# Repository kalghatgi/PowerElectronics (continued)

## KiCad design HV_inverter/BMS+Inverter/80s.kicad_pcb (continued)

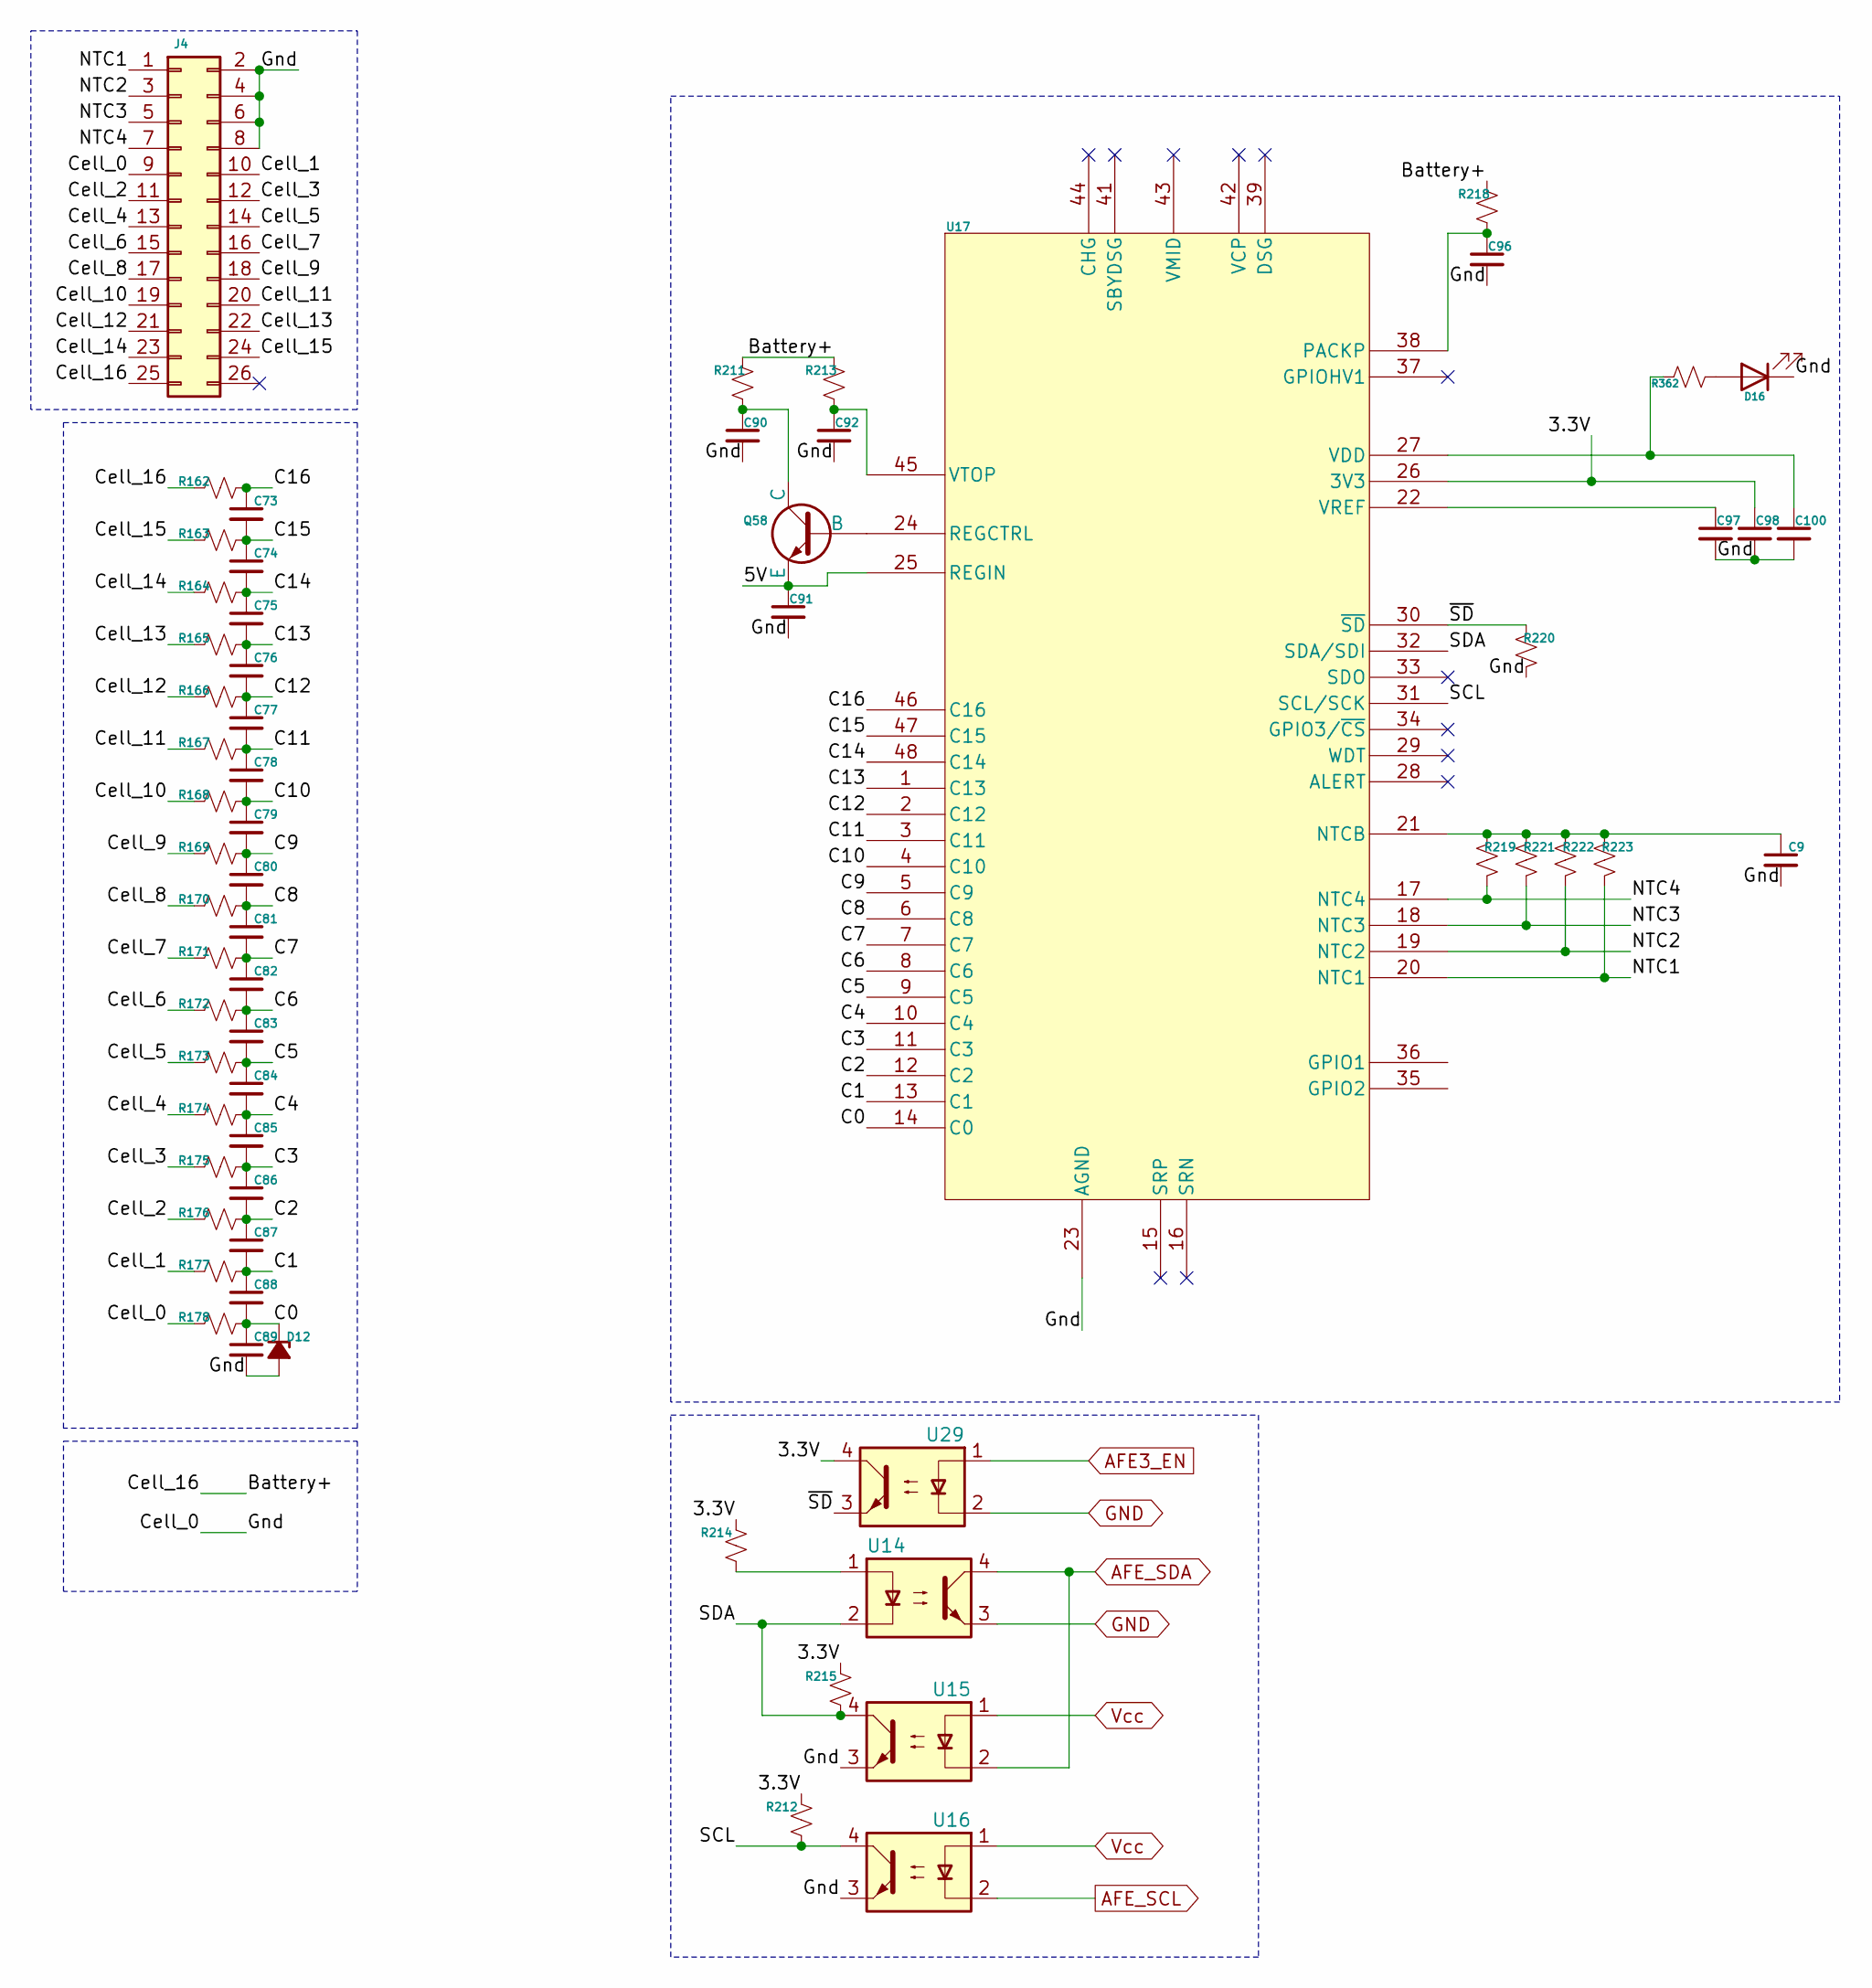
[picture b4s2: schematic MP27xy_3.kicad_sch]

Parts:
C9, C73, C74, C75, C76, C77, C78, C79, C80, C81, C82, C83, C84, C85, C86, C87, C88, C89: 10000pF, >=10V, 0402; C_0402_1005Metric; MPN grm155r61c103ka01d
C90: 1uF, >=100V, 0805; C_0805_2012Metric; MPN grm21bc72a105ke01l
C91: 3.3uF, >=10V, 0402; C_0402_1005Metric
C92: 0.47uF, >=100V, 0805; C_0805_2012Metric; MPN cc0805kkx7r0bb474
C96: 10nF, >=100V, 0805; C_0805_2012Metric; MPN c0805c103k1ractu
C97, C98, C100: 1uF, >=6.3V, 0402; C_0402_1005Metric; MPN cl05a105kq5nnnc
D12: VR=3.3V; D_SOD-323; MPN bzx384c3v3-e3-08
D16: LED-Red 0402; LED_0402_1005Metric
J4: 2x13 pin; IDC-Header_2x13_P2.54mm_Horizontal
Q58: NPN, 80V, 0.5A; SOT-23; MPN mmbt5550lt1g
R162, R163, R164, R165, R166, R167, R168, R169, R170, R171, R172, R173, R174, R175, R176, R177, R178: 1K, >=62.5mW, 0402; R_0402_1005Metric; MPN mcwr04x1001ftl
R211: 500E, >=100mW, 0603; R_0603_1608Metric; MPN rt0603brc07500rl
R212, R214, R215: 1.5K, >=62.5mW, 0402; R_0402_1005Metric; MPN mcwr04x1501ftl
R213: 20E, >=100mW, 0603; R_0603_1608Metric; MPN mcwr06x20r0ftl
R218: 100E, >=100mW, 0603; R_0603_1608Metric; MPN mcwr06x101-jtl
R219, R220, R221, R222, R223, R362: 10K, >=62.5mW, 0402; R_0402_1005Metric; MPN mcwr04x1002ftl
U14, U15, U16, U29: PC817; DIP-4_W7.62mm
U17: MP2787; TQFP-48_7x7mm_P0.5mm; MPN MP2787DFP-0001-T

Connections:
/CMU3/3.3V: C98.1, R212.2, R214.2, R215.2, U17.26 (3V3), U29.4
/CMU3/5V: C91.1, Q58.2 (E), U17.25 (REGIN)
/CMU3/Battery+: J4.25, R162.2, R211.2, R213.2, R218.2
/CMU3/C0: C88.2, C89.1, D12.1 (K), R178.1, U17.14 (C0)
/CMU3/C1: C87.2, C88.1, R177.1, U17.13 (C1)
/CMU3/C2: C86.2, C87.1, R176.1, U17.12 (C2)
/CMU3/C3: C85.2, C86.1, R175.1, U17.11 (C3)
/CMU3/C4: C84.2, C85.1, R174.1, U17.10 (C4)
/CMU3/C5: C83.2, C84.1, R173.1, U17.9 (C5)
/CMU3/C6: C82.2, C83.1, R172.1, U17.8 (C6)
/CMU3/C7: C81.2, C82.1, R171.1, U17.7 (C7)
/CMU3/C8: C80.2, C81.1, R170.1, U17.6 (C8)
/CMU3/C9: C79.2, C80.1, R169.1, U17.5 (C9)
/CMU3/C10: C78.2, C79.1, R168.1, U17.4 (C10)
/CMU3/C11: C77.2, C78.1, R167.1, U17.3 (C11)
/CMU3/C12: C76.2, C77.1, R166.1, U17.2 (C12)
/CMU3/C13: C75.2, C76.1, R165.1, U17.1 (C13)
/CMU3/C14: C74.2, C75.1, R164.1, U17.48 (C14)
/CMU3/C15: C73.2, C74.1, R163.1, U17.47 (C15)
/CMU3/C16: C73.1, R162.1, U17.46 (C16)
/CMU3/Cell_0: C9.2, C89.2, C90.2, C91.2, C92.2, C96.2, C97.2, C98.2, C100.2, D12.2 (A), D16.1 (K), J4.2, J4.4, J4.6, J4.8, J4.9, R178.2, R220.2, U15.3, U16.3, U17.23 (AGND)
/CMU3/Cell_1: J4.10, R177.2
/CMU3/Cell_2: J4.11, R176.2
/CMU3/Cell_3: J4.12, R175.2
/CMU3/Cell_4: J4.13, R174.2
/CMU3/Cell_5: J4.14, R173.2
/CMU3/Cell_6: J4.15, R172.2
/CMU3/Cell_7: J4.16, R171.2
/CMU3/Cell_8: J4.17, R170.2
/CMU3/Cell_9: J4.18, R169.2
/CMU3/Cell_10: J4.19, R168.2
/CMU3/Cell_11: J4.20, R167.2
/CMU3/Cell_12: J4.21, R166.2
/CMU3/Cell_13: J4.22, R165.2
/CMU3/Cell_14: J4.23, R164.2
/CMU3/Cell_15: J4.24, R163.2
/CMU3/NTC1: J4.1, R223.2, U17.20 (NTC1)
/CMU3/NTC2: J4.3, R222.2, U17.19 (NTC2)
/CMU3/NTC3: J4.5, R221.2, U17.18 (NTC3)
/CMU3/NTC4: J4.7, R219.2, U17.17 (NTC4)
/CMU3/SCL: R212.1, U16.4, U17.31 (SCL/SCK)
/CMU3/SDA: R215.1, U14.2, U15.4, U17.32 (SDA/SDI)
/CMU3/~SD: R220.1, U17.30 (~SD), U29.3
AFE3_EN: U29.1; also elsewhere on the board
AFE_SCL: U16.2; also elsewhere on the board
AFE_SDA: U14.4, U15.2; also elsewhere on the board
GND: U14.3, U29.2; also elsewhere on the board
unnamed: D16.2 (A), R362.1
unnamed: Q58.1 (B), U17.24 (REGCTRL)
unnamed: C90.1, Q58.3 (C), R211.1
unnamed: R214.1, U14.1
unnamed: C9.1, R219.1, R221.1, R222.1, R223.1, U17.21 (NTCB)
unnamed: C96.1, R218.1, U17.38 (PACKP)
unnamed: C100.1, R362.2, U17.27 (VDD)
unnamed: C97.1, U17.22 (VREF)
unnamed: C92.1, R213.1, U17.45 (VTOP)
Vcc: U15.1, U16.1; also elsewhere on the board

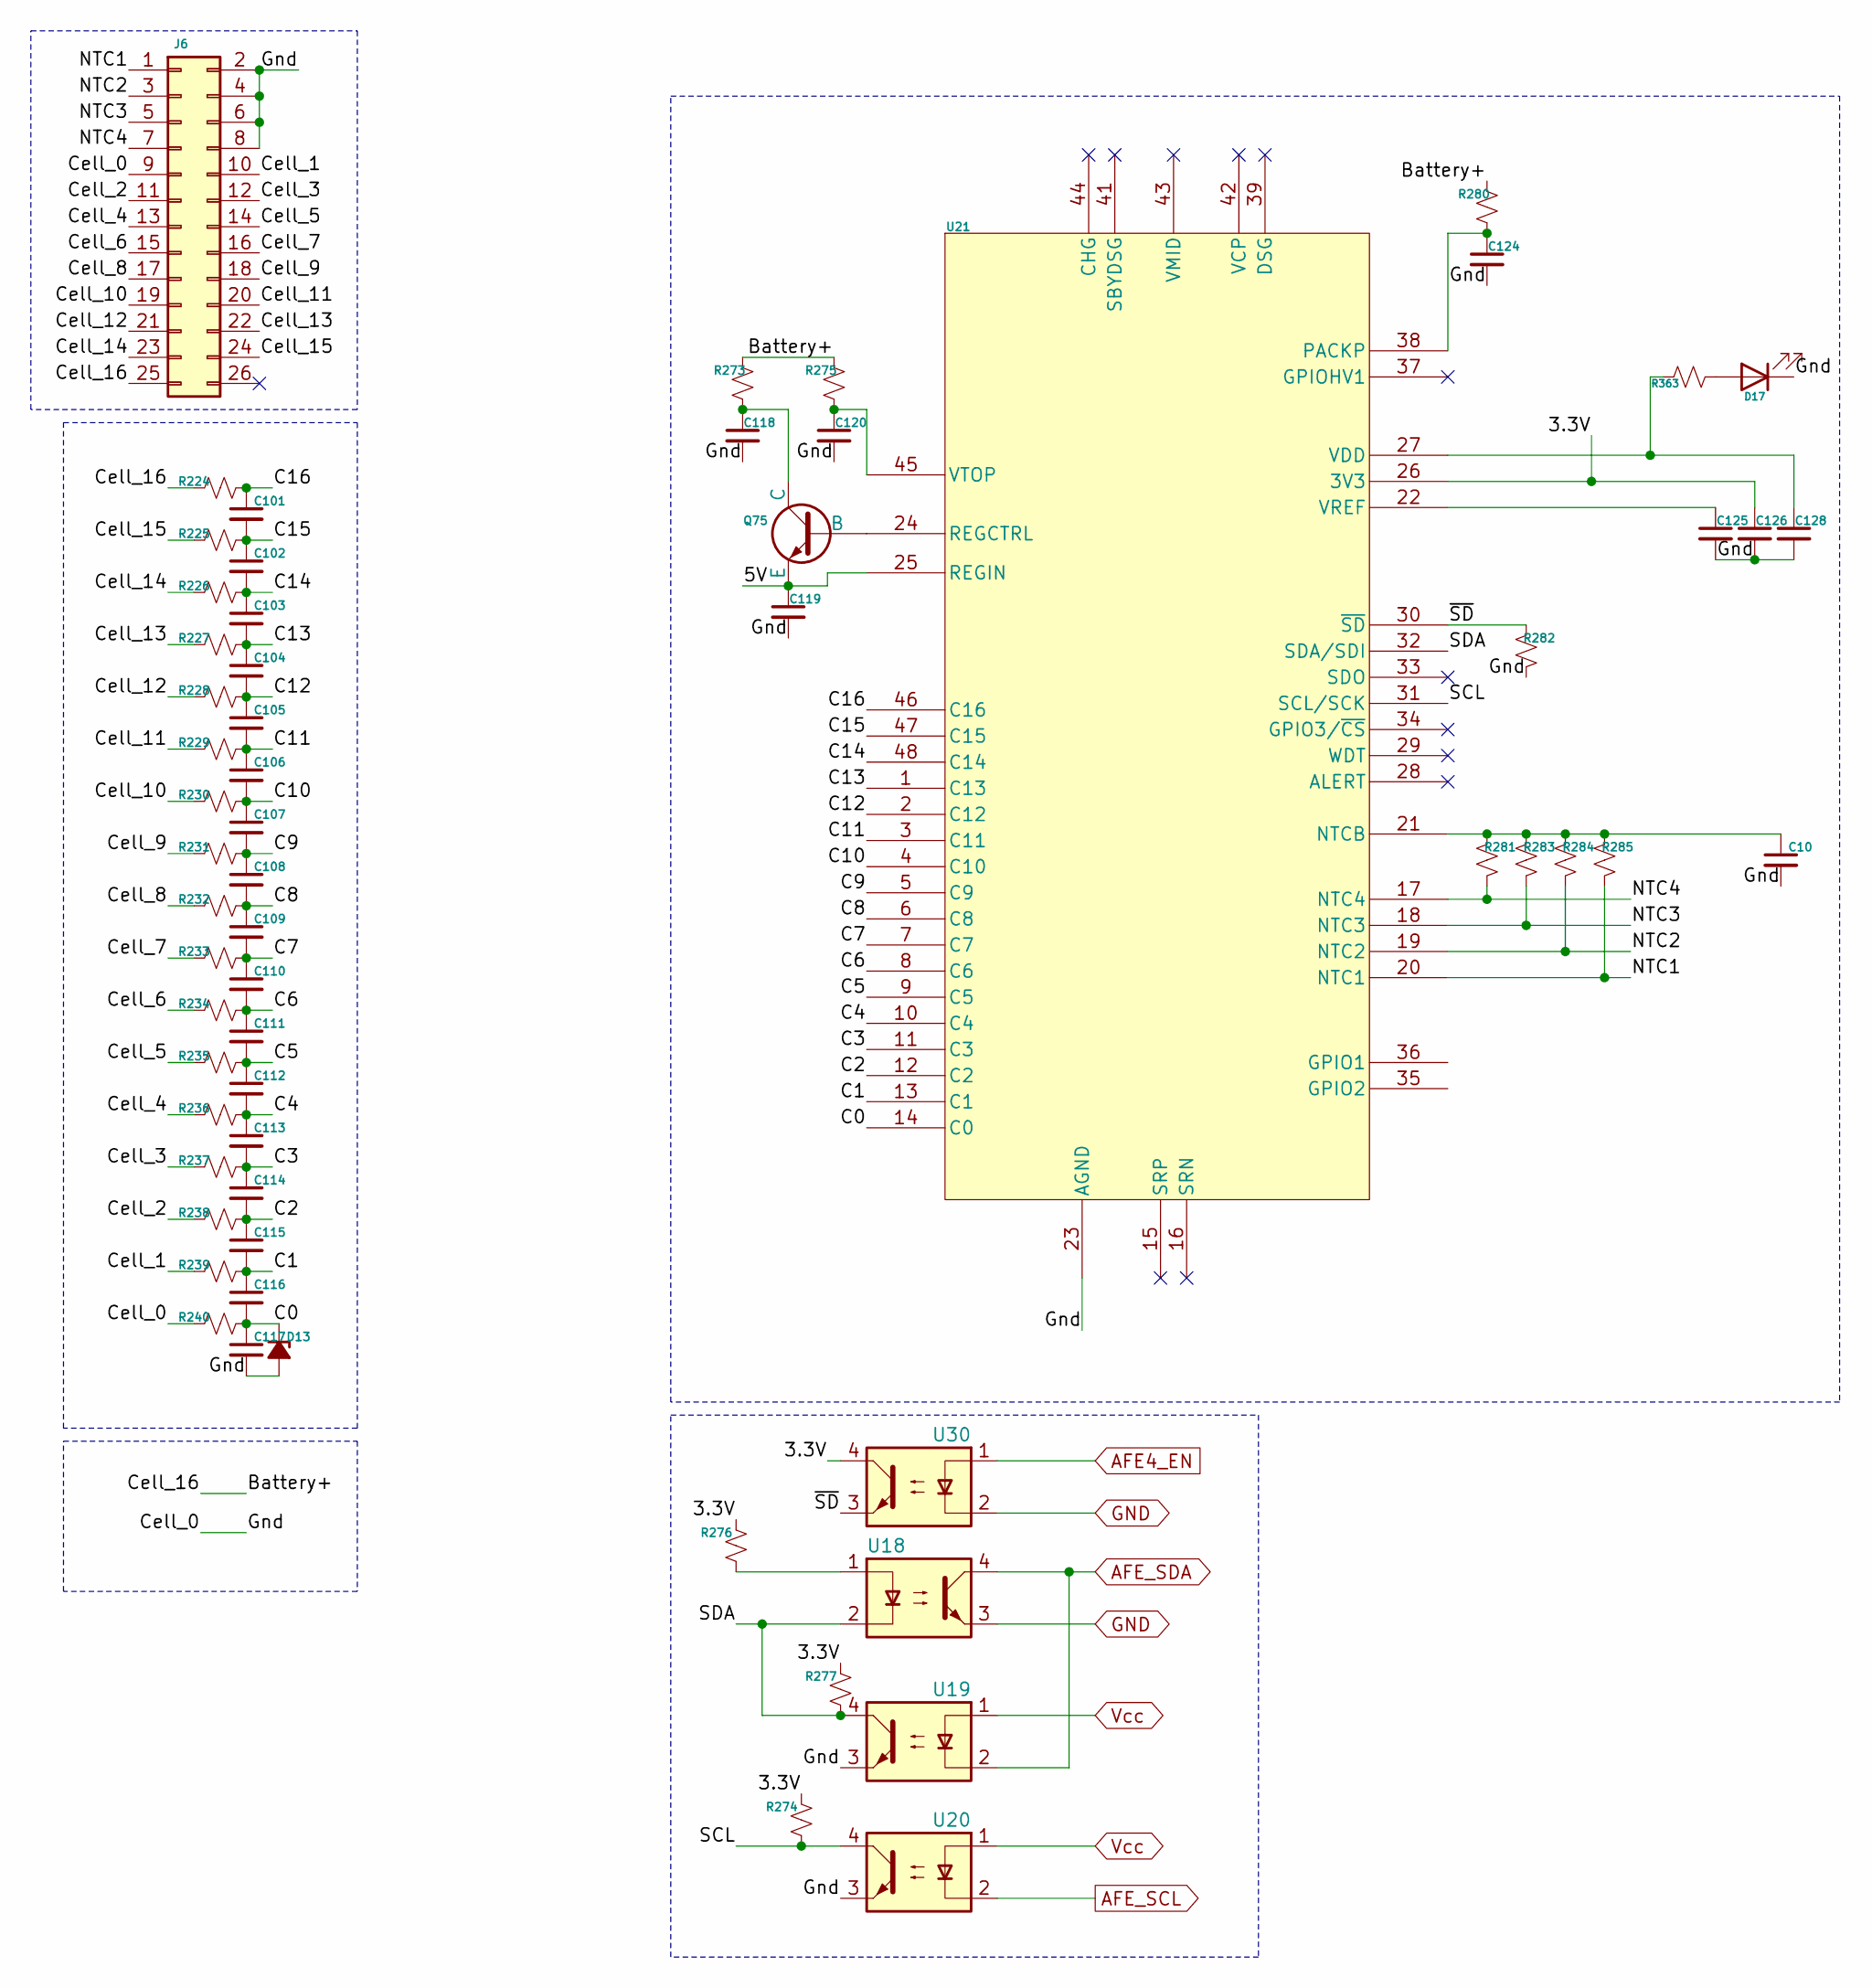
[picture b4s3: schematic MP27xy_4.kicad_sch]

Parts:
C10, C101, C102, C103, C104, C105, C106, C107, C108, C109, C110, C111, C112, C113, C114, C115, C116, C117: 10000pF, >=10V, 0402; C_0402_1005Metric; MPN grm155r61c103ka01d
C118: 1uF, >=100V, 0805; C_0805_2012Metric; MPN grm21bc72a105ke01l
C119: 3.3uF, >=10V, 0402; C_0402_1005Metric
C120: 0.47uF, >=100V, 0805; C_0805_2012Metric; MPN cc0805kkx7r0bb474
C124: 10nF, >=100V, 0805; C_0805_2012Metric; MPN c0805c103k1ractu
C125, C126, C128: 1uF, >=6.3V, 0402; C_0402_1005Metric; MPN cl05a105kq5nnnc
D13: VR=3.3V; D_SOD-323; MPN bzx384c3v3-e3-08
D17: LED-Red 0402; LED_0402_1005Metric
J6: 2x13 pin; IDC-Header_2x13_P2.54mm_Horizontal
Q75: NPN, 80V, 0.5A; SOT-23; MPN mmbt5550lt1g
R224, R225, R226, R227, R228, R229, R230, R231, R232, R233, R234, R235, R236, R237, R238, R239, R240: 1K, >=62.5mW, 0402; R_0402_1005Metric; MPN mcwr04x1001ftl
R273: 500E, >=100mW, 0603; R_0603_1608Metric; MPN rt0603brc07500rl
R274, R276, R277: 1.5K, >=62.5mW, 0402; R_0402_1005Metric; MPN mcwr04x1501ftl
R275: 20E, >=100mW, 0603; R_0603_1608Metric; MPN mcwr06x20r0ftl
R280: 100E, >=100mW, 0603; R_0603_1608Metric; MPN mcwr06x101-jtl
R281, R282, R283, R284, R285, R363: 10K, >=62.5mW, 0402; R_0402_1005Metric; MPN mcwr04x1002ftl
U18, U19, U20, U30: PC817; DIP-4_W7.62mm
U21: MP2787; TQFP-48_7x7mm_P0.5mm; MPN MP2787DFP-0001-T

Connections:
/CMU4/3.3V: C126.1, R274.2, R276.2, R277.2, U21.26 (3V3), U30.4
/CMU4/5V: C119.1, Q75.2 (E), U21.25 (REGIN)
/CMU4/Battery+: J6.25, R224.2, R273.2, R275.2, R280.2
/CMU4/C0: C116.2, C117.1, D13.1 (K), R240.1, U21.14 (C0)
/CMU4/C1: C115.2, C116.1, R239.1, U21.13 (C1)
/CMU4/C2: C114.2, C115.1, R238.1, U21.12 (C2)
/CMU4/C3: C113.2, C114.1, R237.1, U21.11 (C3)
/CMU4/C4: C112.2, C113.1, R236.1, U21.10 (C4)
/CMU4/C5: C111.2, C112.1, R235.1, U21.9 (C5)
/CMU4/C6: C110.2, C111.1, R234.1, U21.8 (C6)
/CMU4/C7: C109.2, C110.1, R233.1, U21.7 (C7)
/CMU4/C8: C108.2, C109.1, R232.1, U21.6 (C8)
/CMU4/C9: C107.2, C108.1, R231.1, U21.5 (C9)
/CMU4/C10: C106.2, C107.1, R230.1, U21.4 (C10)
/CMU4/C11: C105.2, C106.1, R229.1, U21.3 (C11)
/CMU4/C12: C104.2, C105.1, R228.1, U21.2 (C12)
/CMU4/C13: C103.2, C104.1, R227.1, U21.1 (C13)
/CMU4/C14: C102.2, C103.1, R226.1, U21.48 (C14)
/CMU4/C15: C101.2, C102.1, R225.1, U21.47 (C15)
/CMU4/C16: C101.1, R224.1, U21.46 (C16)
/CMU4/Cell_0: C10.2, C117.2, C118.2, C119.2, C120.2, C124.2, C125.2, C126.2, C128.2, D13.2 (A), D17.1 (K), J6.2, J6.4, J6.6, J6.8, J6.9, R240.2, R282.2, U19.3, U20.3, U21.23 (AGND)
/CMU4/Cell_1: J6.10, R239.2
/CMU4/Cell_2: J6.11, R238.2
/CMU4/Cell_3: J6.12, R237.2
/CMU4/Cell_4: J6.13, R236.2
/CMU4/Cell_5: J6.14, R235.2
/CMU4/Cell_6: J6.15, R234.2
/CMU4/Cell_7: J6.16, R233.2
/CMU4/Cell_8: J6.17, R232.2
/CMU4/Cell_9: J6.18, R231.2
/CMU4/Cell_10: J6.19, R230.2
/CMU4/Cell_11: J6.20, R229.2
/CMU4/Cell_12: J6.21, R228.2
/CMU4/Cell_13: J6.22, R227.2
/CMU4/Cell_14: J6.23, R226.2
/CMU4/Cell_15: J6.24, R225.2
/CMU4/NTC1: J6.1, R285.2, U21.20 (NTC1)
/CMU4/NTC2: J6.3, R284.2, U21.19 (NTC2)
/CMU4/NTC3: J6.5, R283.2, U21.18 (NTC3)
/CMU4/NTC4: J6.7, R281.2, U21.17 (NTC4)
/CMU4/SCL: R274.1, U20.4, U21.31 (SCL/SCK)
/CMU4/SDA: R277.1, U18.2, U19.4, U21.32 (SDA/SDI)
/CMU4/~SD: R282.1, U21.30 (~SD), U30.3
AFE4_EN: U30.1; also elsewhere on the board
AFE_SCL: U20.2; also elsewhere on the board
AFE_SDA: U18.4, U19.2; also elsewhere on the board
GND: U18.3, U30.2; also elsewhere on the board
unnamed: D17.2 (A), R363.1
unnamed: Q75.1 (B), U21.24 (REGCTRL)
unnamed: C118.1, Q75.3 (C), R273.1
unnamed: R276.1, U18.1
unnamed: C10.1, R281.1, R283.1, R284.1, R285.1, U21.21 (NTCB)
unnamed: C124.1, R280.1, U21.38 (PACKP)
unnamed: C128.1, R363.2, U21.27 (VDD)
unnamed: C125.1, U21.22 (VREF)
unnamed: C120.1, R275.1, U21.45 (VTOP)
Vcc: U19.1, U20.1; also elsewhere on the board

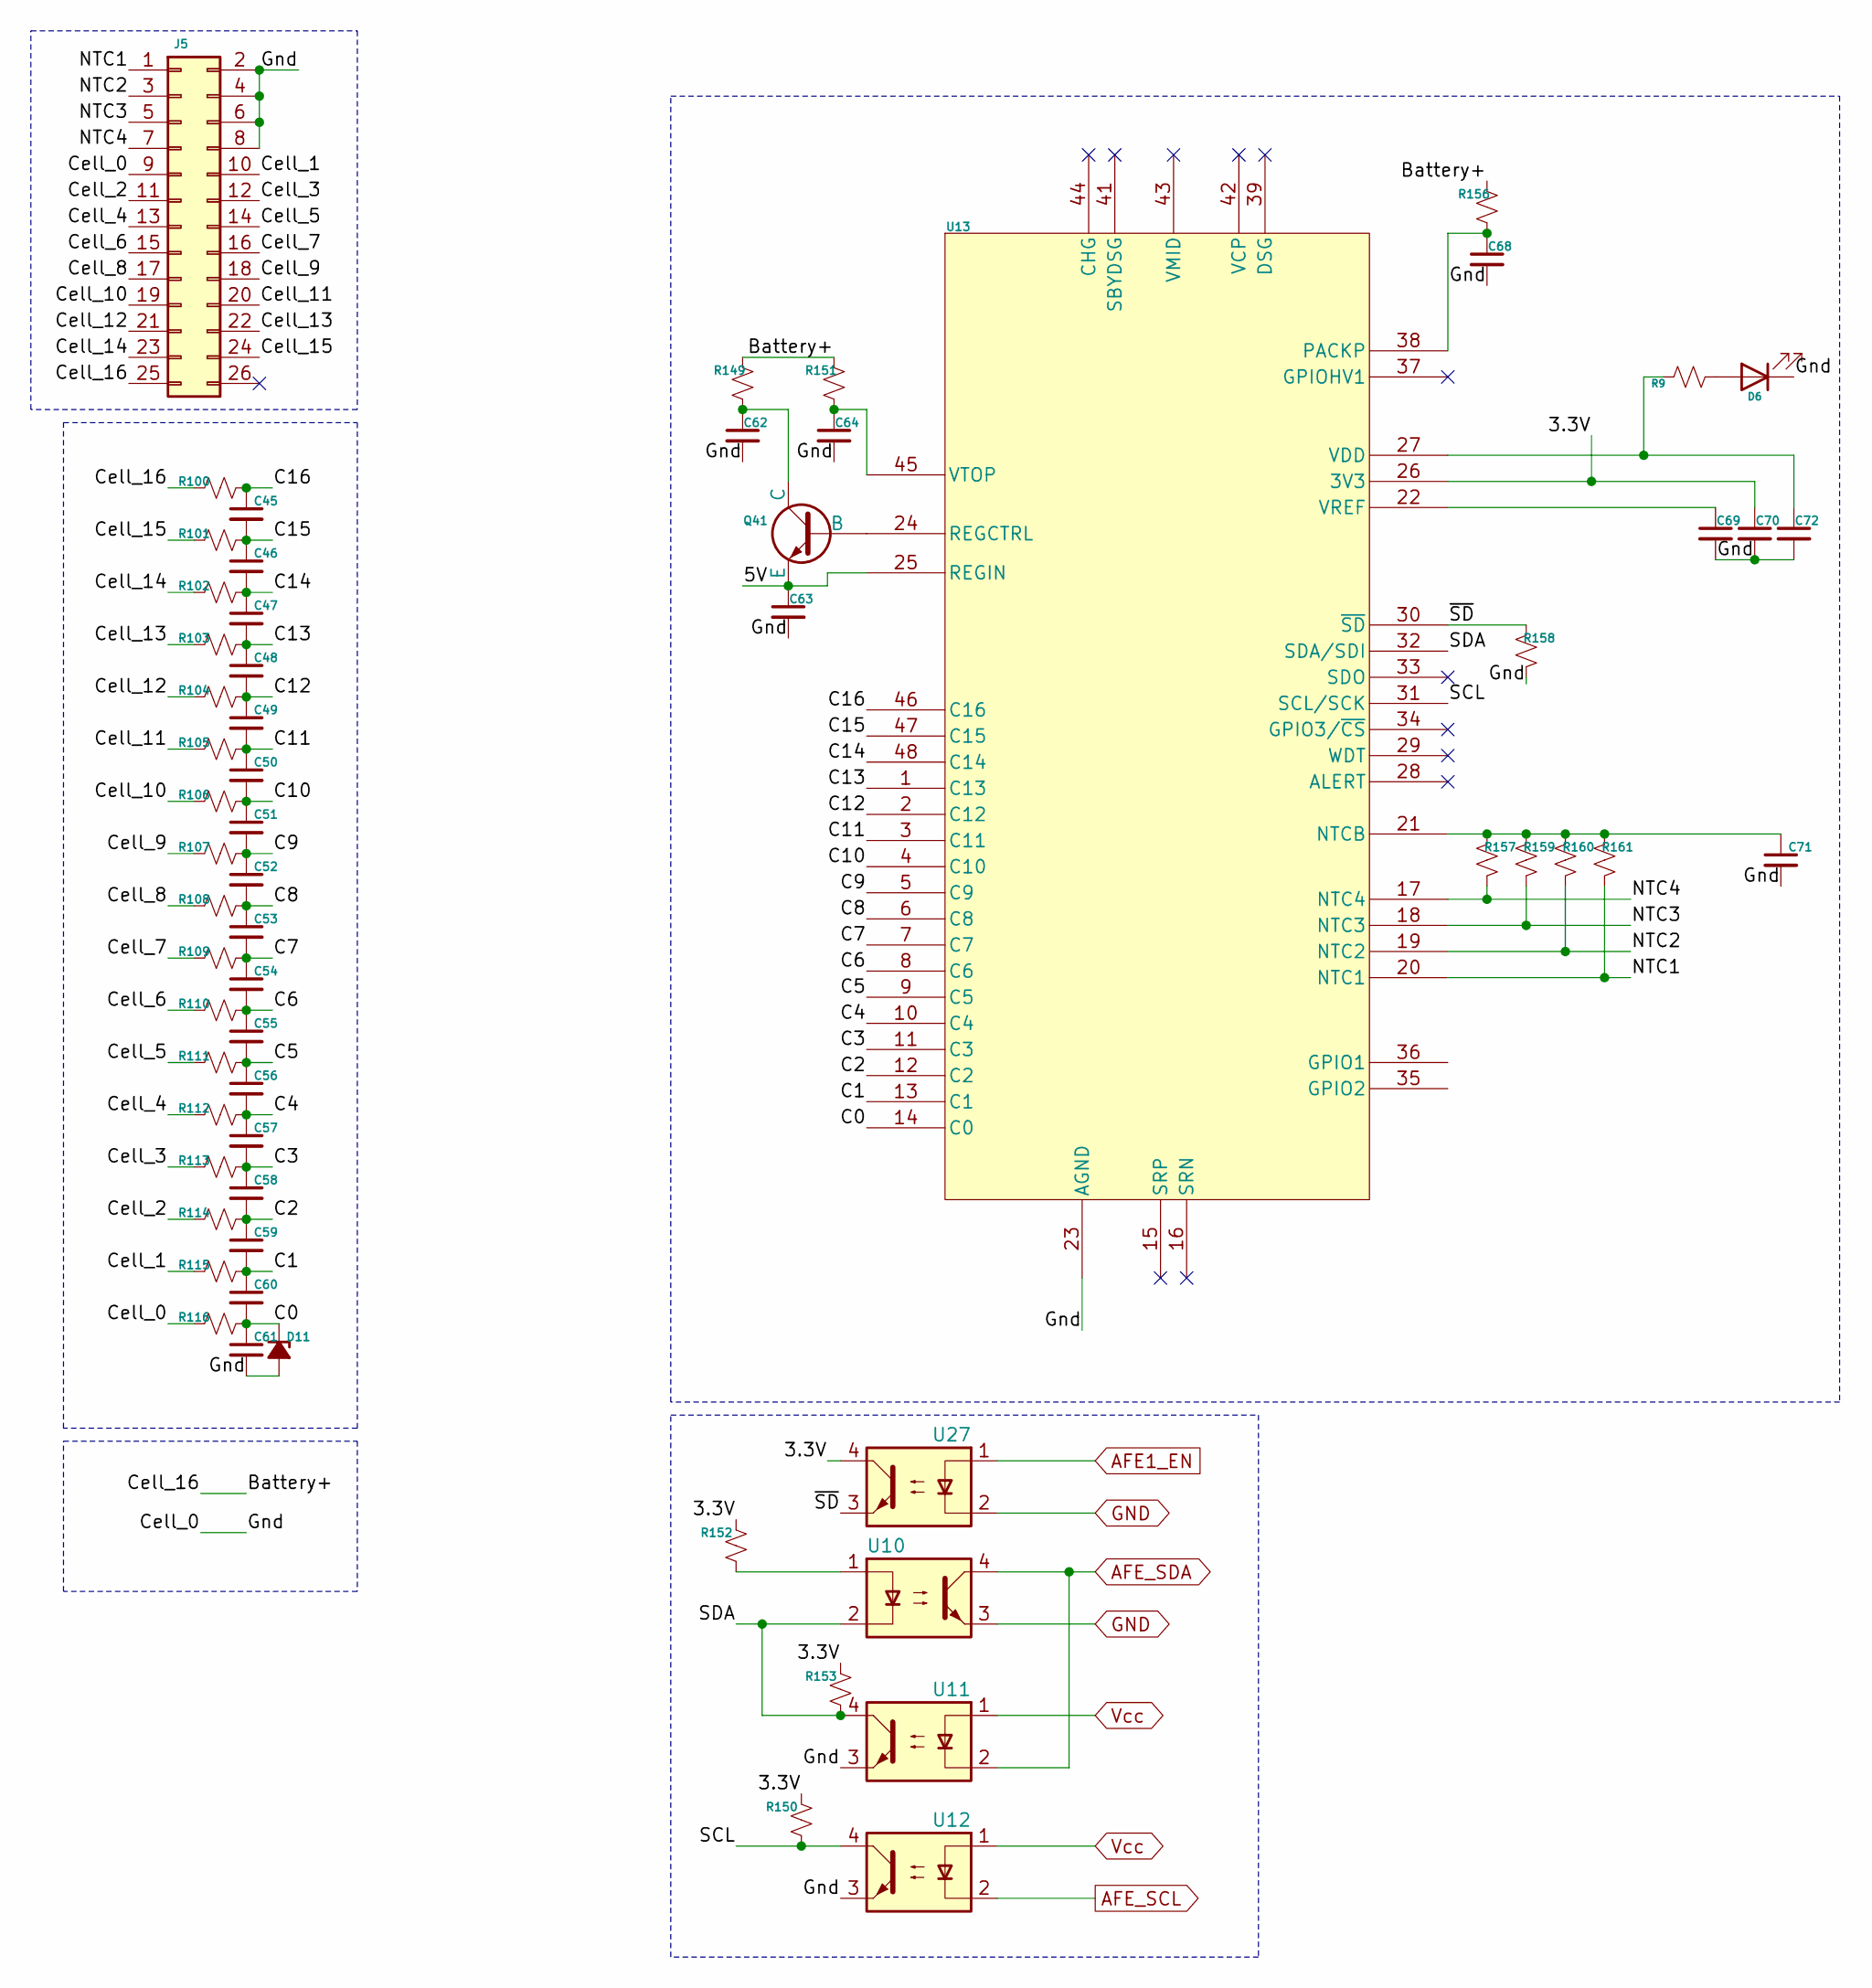
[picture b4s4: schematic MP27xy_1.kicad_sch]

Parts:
C45, C46, C47, C48, C49, C50, C51, C52, C53, C54, C55, C56, C57, C58, C59, C60, C61, C71: 10000pF, >=10V, 0402; C_0402_1005Metric; MPN grm155r61c103ka01d
C62: 1uF, >=100V, 0805; C_0805_2012Metric; MPN grm21bc72a105ke01l
C63: 3.3uF, >=10V, 0402; C_0402_1005Metric
C64: 0.47uF, >=100V, 0805; C_0805_2012Metric; MPN cc0805kkx7r0bb474
C68: 10nF, >=100V, 0805; C_0805_2012Metric; MPN c0805c103k1ractu
C69, C70, C72: 1uF, >=6.3V, 0402; C_0402_1005Metric; MPN cl05a105kq5nnnc
D6: LED-Red 0402; LED_0402_1005Metric
D11: VR=3.3V; D_SOD-323; MPN bzx384c3v3-e3-08
J5: 2x13 pin; IDC-Header_2x13_P2.54mm_Horizontal
Q41: NPN, 80V, 0.5A; SOT-23; MPN mmbt5550lt1g
R9, R157, R158, R159, R160, R161: 10K, >=62.5mW, 0402; R_0402_1005Metric; MPN mcwr04x1002ftl
R100, R101, R102, R103, R104, R105, R106, R107, R108, R109, R110, R111, R112, R113, R114, R115, R116: 1K, >=62.5mW, 0402; R_0402_1005Metric; MPN mcwr04x1001ftl
R149: 500E, >=100mW, 0603; R_0603_1608Metric; MPN rt0603brc07500rl
R150, R152, R153: 1.5K, >=62.5mW, 0402; R_0402_1005Metric; MPN mcwr04x1501ftl
R151: 20E, >=100mW, 0603; R_0603_1608Metric; MPN mcwr06x20r0ftl
R156: 100E, >=100mW, 0603; R_0603_1608Metric; MPN mcwr06x101-jtl
U10, U11, U12, U27: PC817; DIP-4_W7.62mm
U13: MP2787; TQFP-48_7x7mm_P0.5mm; MPN MP2787DFP-0001-T

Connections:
/CMU1/3.3V: C70.1, R150.2, R152.2, R153.2, U13.26 (3V3), U27.4
/CMU1/5V: C63.1, Q41.2 (E), U13.25 (REGIN)
/CMU1/Battery+: J5.25, R100.2, R149.2, R151.2, R156.2
/CMU1/C0: C60.2, C61.1, D11.1 (K), R116.1, U13.14 (C0)
/CMU1/C1: C59.2, C60.1, R115.1, U13.13 (C1)
/CMU1/C2: C58.2, C59.1, R114.1, U13.12 (C2)
/CMU1/C3: C57.2, C58.1, R113.1, U13.11 (C3)
/CMU1/C4: C56.2, C57.1, R112.1, U13.10 (C4)
/CMU1/C5: C55.2, C56.1, R111.1, U13.9 (C5)
/CMU1/C6: C54.2, C55.1, R110.1, U13.8 (C6)
/CMU1/C7: C53.2, C54.1, R109.1, U13.7 (C7)
/CMU1/C8: C52.2, C53.1, R108.1, U13.6 (C8)
/CMU1/C9: C51.2, C52.1, R107.1, U13.5 (C9)
/CMU1/C10: C50.2, C51.1, R106.1, U13.4 (C10)
/CMU1/C11: C49.2, C50.1, R105.1, U13.3 (C11)
/CMU1/C12: C48.2, C49.1, R104.1, U13.2 (C12)
/CMU1/C13: C47.2, C48.1, R103.1, U13.1 (C13)
/CMU1/C14: C46.2, C47.1, R102.1, U13.48 (C14)
/CMU1/C15: C45.2, C46.1, R101.1, U13.47 (C15)
/CMU1/C16: C45.1, R100.1, U13.46 (C16)
/CMU1/Cell_0: C61.2, C62.2, C63.2, C64.2, C68.2, C69.2, C70.2, C71.2, C72.2, D6.1 (K), D11.2 (A), J5.2, J5.4, J5.6, J5.8, J5.9, R116.2, R158.2, U11.3, U12.3, U13.23 (AGND)
/CMU1/Cell_1: J5.10, R115.2
/CMU1/Cell_2: J5.11, R114.2
/CMU1/Cell_3: J5.12, R113.2
/CMU1/Cell_4: J5.13, R112.2
/CMU1/Cell_5: J5.14, R111.2
/CMU1/Cell_6: J5.15, R110.2
/CMU1/Cell_7: J5.16, R109.2
/CMU1/Cell_8: J5.17, R108.2
/CMU1/Cell_9: J5.18, R107.2
/CMU1/Cell_10: J5.19, R106.2
/CMU1/Cell_11: J5.20, R105.2
/CMU1/Cell_12: J5.21, R104.2
/CMU1/Cell_13: J5.22, R103.2
/CMU1/Cell_14: J5.23, R102.2
/CMU1/Cell_15: J5.24, R101.2
/CMU1/NTC1: J5.1, R161.2, U13.20 (NTC1)
/CMU1/NTC2: J5.3, R160.2, U13.19 (NTC2)
/CMU1/NTC3: J5.5, R159.2, U13.18 (NTC3)
/CMU1/NTC4: J5.7, R157.2, U13.17 (NTC4)
/CMU1/SCL: R150.1, U12.4, U13.31 (SCL/SCK)
/CMU1/SDA: R153.1, U10.2, U11.4, U13.32 (SDA/SDI)
/CMU1/~SD: R158.1, U13.30 (~SD), U27.3
AFE1_EN: U27.1; also elsewhere on the board
AFE_SCL: U12.2; also elsewhere on the board
AFE_SDA: U10.4, U11.2; also elsewhere on the board
GND: U10.3, U27.2; also elsewhere on the board
unnamed: D6.2 (A), R9.1
unnamed: Q41.1 (B), U13.24 (REGCTRL)
unnamed: C62.1, Q41.3 (C), R149.1
unnamed: R152.1, U10.1
unnamed: C71.1, R157.1, R159.1, R160.1, R161.1, U13.21 (NTCB)
unnamed: C68.1, R156.1, U13.38 (PACKP)
unnamed: C72.1, R9.2, U13.27 (VDD)
unnamed: C69.1, U13.22 (VREF)
unnamed: C64.1, R151.1, U13.45 (VTOP)
Vcc: U11.1, U12.1; also elsewhere on the board
